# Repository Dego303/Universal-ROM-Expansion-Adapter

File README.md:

# Universal ROM Expansion Adapter

Open-hardware adapter for using larger 28-pin 8-bit EPROM, EEPROM, and flash-compatible memory devices in vintage equipment.

> [!CAUTION]
> **v0.8 is invalidated. Do not fabricate, assemble, install, or power it.** Real-hardware testing exposed mirrored DIP-28 pad numbering on both interfaces. See [Known Issues](docs/KNOWN_ISSUES.md).

**v0.9 is a corrected prototype.** The U1 memory socket and H1 host interface follow the standard DIP-28 top-view numbering. KiCad 10.0.8 DRC and design-file verification passed. The v0.9 board awaits physical assembly, continuity checks, and first power-up.

The board passes the common address, data, chip-enable, output-enable, power, and ground pins directly between the host socket and the replacement memory. Pins 1, 26, and 27 are configurable. The external header exposes A13, A14, and A15 for bank selection.

## Why this exists

Vintage systems use 27C-series EPROMs for operating systems, program code, configuration data, and lookup tables. This adapter provides a compact development and preservation tool when a larger replacement memory is needed or additional address lines must be controlled externally.

This repository contains **hardware design files only**. Only distribute binary images when you have the legal right to do so.

## Features

- Designed for host sockets wired for 27C64, 27C128, or 27C256.
- Read-mode configurations for 27C256, SST27SF256, AT28C256 and pin-compatible 28C256, 27C512, and SST27SF512.
- A 1x4 header for A13, A14, A15, and GND, with 10 kOhm pull-downs for a low-bank default.
- 100 nF local decoupling, hand-solderable 0805 passives, and solder jumpers.
- 24 x 41 mm, two-layer PCB with KiCad source, BOM, and fabrication files.

## Files and instructions

- [Download the v0.9 prototype test package and fabrication files](https://github.com/Dego303/Universal-ROM-Expansion-Adapter/releases/tag/v0.9)
- [KiCad project](hardware/kicad/Universal-ROM-Expansion-Adapter-v0.9.kicad_pro) and [BOM](hardware/bom/BOM.csv)
- [Jumper Guide](docs/JUMPER_GUIDE.md), [Assembly and Test Guide](docs/ASSEMBLY.md), [Compatibility](docs/COMPATIBILITY.md), and [ROM Image Preparation](docs/ROM_IMAGE_PREPARATION.md)
- [v0.9 change and verification report](validation/V0.9_VERIFICATION.md) and [KiCad DRC report](validation/KiCad_DRC_v0.9.rpt)
- [Gerber and Excellon files](hardware/gerber/README.md)

Close **exactly one** jumper in each group: `P1`, `P26`, and `P27`.

## Prototype fabrication

Use the v0.9 fabrication files for prototype testing. Suggested settings are two-layer FR-4, 1.6 mm thickness, 1 oz copper, and lead-free HASL or ENIG. Follow the unpowered checks in the assembly guide before fitting the prototype into a powered setup.

## Licence

Hardware source and documentation are released under the CERN Open Hardware Licence Version 2 - Permissive (`CERN-OHL-P-2.0`).

## Search terms

27C64, 27C128, 27C256, 27C512, AT28C256, 28C256, SST27SF256, SST27SF512, EPROM adapter, EEPROM adapter, flash ROM adapter, ROM expansion, bank switching, bank selection, vintage hardware, synthesizer repair, arcade repair, retro computing, embedded systems.

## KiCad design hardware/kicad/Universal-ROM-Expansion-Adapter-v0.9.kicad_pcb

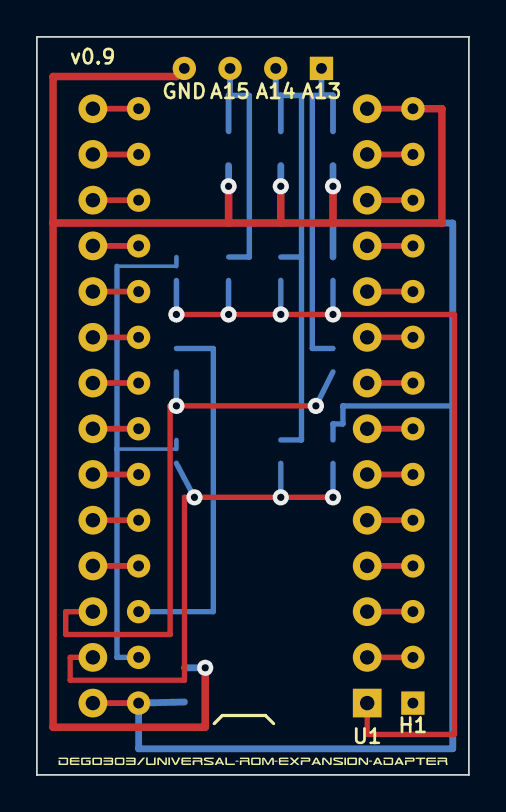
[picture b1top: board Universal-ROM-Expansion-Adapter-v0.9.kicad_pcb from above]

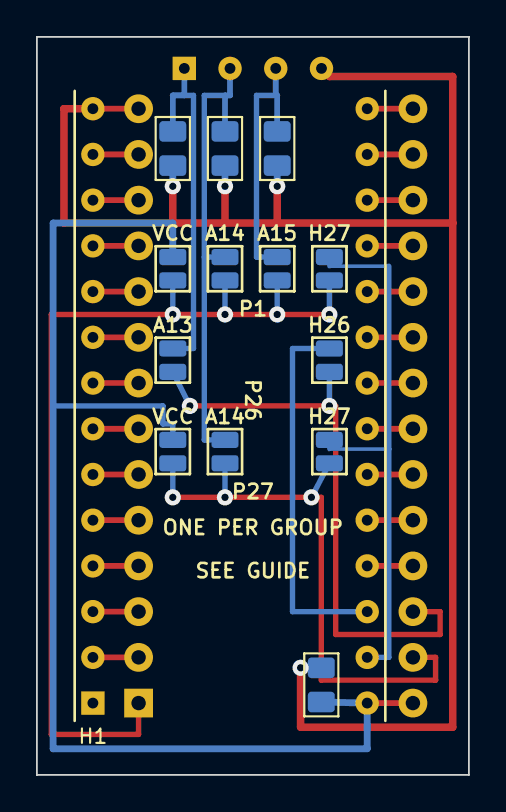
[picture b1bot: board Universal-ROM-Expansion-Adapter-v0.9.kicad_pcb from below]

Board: 2 copper layers, 24.0 x 41.0 mm, 16 parts (13 on the bottom side), 33 nets.

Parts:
C1: 100n; C_0805_Hand
H1: 350-10-114 x2; MillMax_350-10-114-00-006000_x2
JP1A, JP1B, JP1C, JP1D, JP26A, JP26B, JP27A, JP27B, JP27C: OPEN; SolderJumper_Hand
J_EXT: 350-10-104-00-001000; MillMax_350-10-104-00-001000
R1, R2, R3: 10k; R_0805_Hand
U1: 110-93-628-41-001000; MillMax_110-93-628-41-001000

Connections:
A0: H1.10, U1.10
A1: H1.9, U1.9
A2: H1.8, U1.8
A3: H1.7, U1.7
A4: H1.6, U1.6
A5: H1.5, U1.5
A6: H1.4, U1.4
A7: H1.3, U1.3
A8: H1.25, U1.25
A9: H1.24, U1.24
A10: H1.21, U1.21
A11: H1.23, U1.23
A12: H1.2, U1.2
CE#: H1.20, U1.20
D0: H1.11, U1.11
D1: H1.12, U1.12
D2: H1.13, U1.13
D3: H1.15, U1.15
D4: H1.16, U1.16
D5: H1.17, U1.17
D6: H1.18, U1.18
D7: H1.19, U1.19
EXT_A13: JP26B.1, J_EXT.1 (A13), R1.1
EXT_A14: JP1C.1, JP27B.1, J_EXT.2 (A14), R2.1
EXT_A15: JP1D.1, J_EXT.3 (A15), R3.1
GND: C1.2, H1.14, J_EXT.4 (GND), R1.2, R2.2, R3.2, U1.14
H1_P26: H1.26, JP26A.1
H1_P27: H1.27, JP1B.1, JP27A.1
OE#: H1.22, U1.22
U1_P1: JP1A.2, JP1B.2, JP1C.2, JP1D.2, U1.1
U1_P26: JP26A.2, JP26B.2, U1.26
U1_P27: JP27A.2, JP27B.2, JP27C.2, U1.27
VCC: C1.1, H1.28, JP1A.1, JP27C.1, U1.28

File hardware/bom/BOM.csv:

Designator,Qty,Manufacturer,Part number,Description
"H1L, H1R",2,Mill-Max,350-10-114-00-006000,"1x14 round male machine-pin strips, 2.54 mm pitch"
U1,1,Mill-Max,110-93-628-41-001000,28-pin 600 mil precision DIP socket
J_EXT,1,Mill-Max,350-10-104-00-001000,"1x4 round pin header, 2.54 mm pitch"
R1-R3,3,Yageo,RC0805FR-0710KL,"10 kOhm, 1%, 0805 pull-down"
C1,1,Yageo,CC0805KRX7R9BB104,"100 nF, X7R, 0805 decoupling capacitor"
